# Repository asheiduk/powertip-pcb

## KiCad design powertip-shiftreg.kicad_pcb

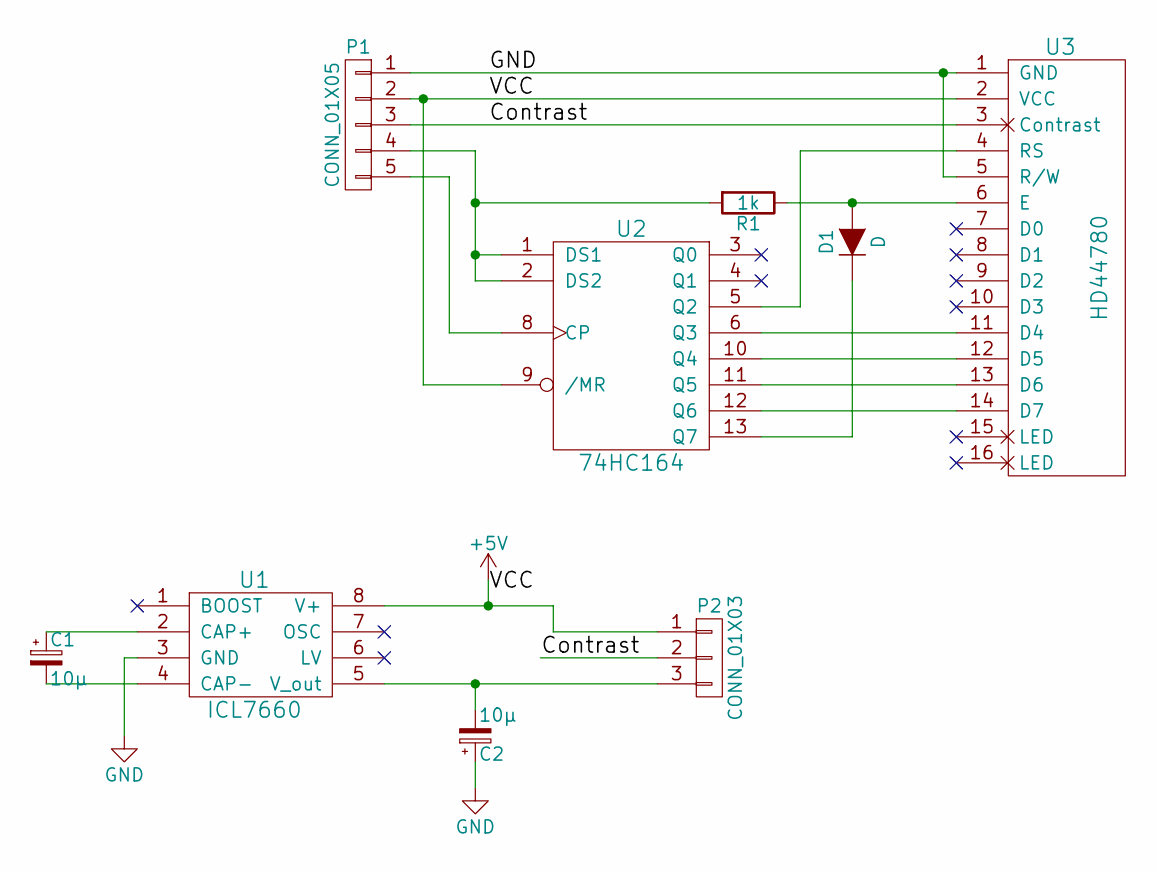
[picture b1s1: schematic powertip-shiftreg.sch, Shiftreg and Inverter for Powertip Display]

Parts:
C1, C2: 10µ; C_Radial_D5_L6_P2.5
D1: D; Diode_DO-35_SOD27_Horizontal_RM10
P1: CONN_01X05; Pin_Header_Straight_1x05
P2: CONN_01X03; Pin_Header_Straight_1x03
R1: 1k; Resistor_Horizontal_RM15mm
U1: ICL7660; DIP-8_W7.62mm
U2: 74HC164; DIP-14_W7.62mm
U3: HD44780; Pin_Header_Straight_1x16

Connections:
+5V: P1.2, P2.1, U1.8 (V+), U2.9 (/MR), U2.14 (VCC), U3.2 (VCC)
/Contrast: P1.3, P2.2, U3.3 (Contrast)
GND: C2.1, P1.1, U1.3 (GND), U2.7 (GND), U3.1 (GND), U3.5 (R/W)
unnamed: C1.1, U1.2 (CAP+)
unnamed: C1.2, U1.4 (CAP-)
unnamed: C2.2, P2.3, U1.5 (V_out)
unnamed: D1.1 (K), U2.13 (Q7)
unnamed: D1.2 (A), R1.1, U3.6 (E)
unnamed: P1.4, R1.2, U2.1 (DS1), U2.2 (DS2)
unnamed: P1.5, U2.8 (CP)
unnamed: U2.5 (Q2), U3.4 (RS)
unnamed: U2.6 (Q3), U3.11 (D4)
unnamed: U2.10 (Q4), U3.12 (D5)
unnamed: U2.11 (Q5), U3.13 (D6)
unnamed: U2.12 (Q6), U3.14 (D7)

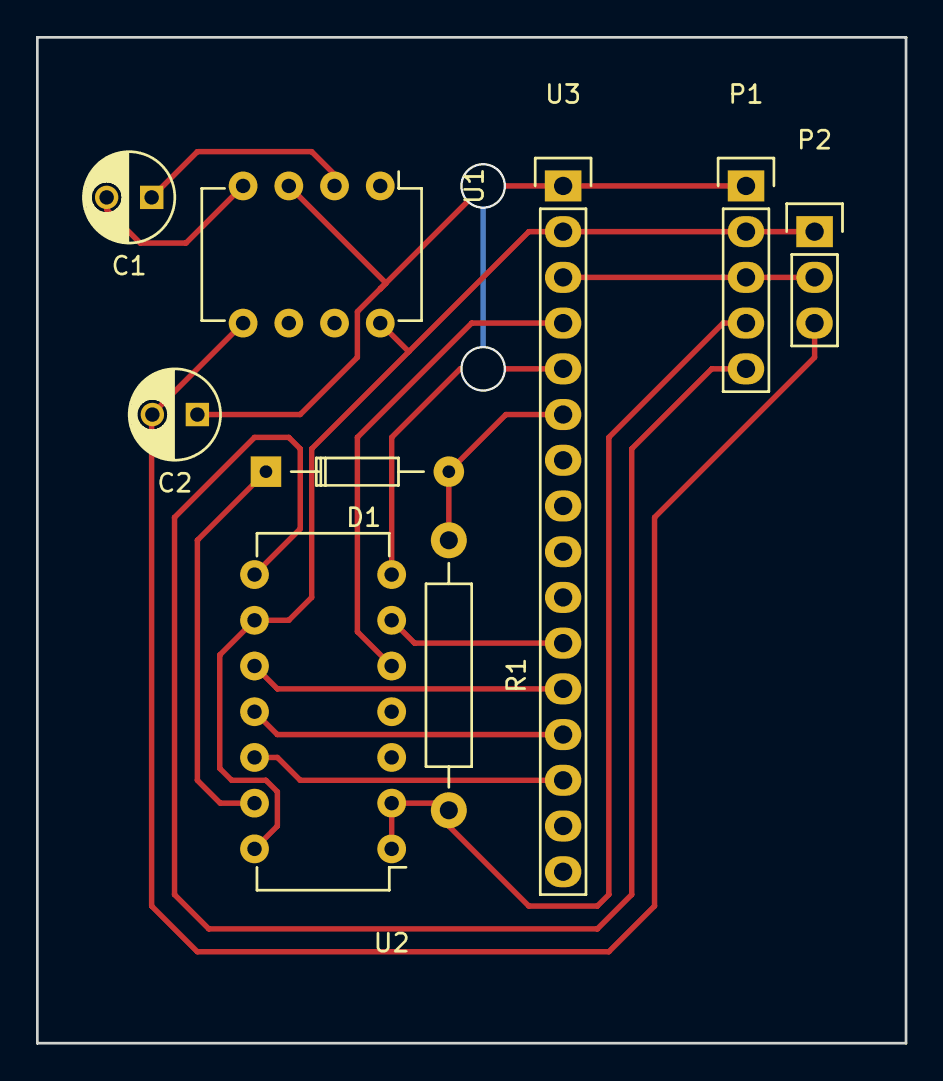
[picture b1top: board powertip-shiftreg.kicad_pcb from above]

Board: 2 copper layers, 48.3 x 55.9 mm, 9 parts (0 on the bottom side), 15 nets.

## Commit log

2016-11-25 first checkin
2016-11-27 - Board ist jetzt unter dem Display plaziert. - 3er Stecker hat jetzt VCC+, Contrast, VCC-
